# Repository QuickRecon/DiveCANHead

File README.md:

# DiveCAN Head

Open hardware and firmware for a DiveCAN-compatible closed-circuit rebreather
PPO₂ monitor and controller. The firmware supports analog galvanic cells,
DiveO2 and O2S digital cells, solenoid control, runtime configuration,
diagnostics, and persistent telemetry.

## Current development

Active firmware lives in [`Firmware/`](Firmware/) and runs **Zephyr RTOS** on
an STM32L431. It uses MCUboot for updates, Zephyr settings/NVS for persistent
configuration, and flash-backed logs for telemetry and diagnostic text.
The former `STM32/` FreeRTOS application and its build/test directories are no
longer part of this checkout. Earlier implementations and their documentation
remain available in Git history.

Two board targets are defined:

| Board | West target | External storage and power |
|---|---|---|
| DiveCAN Jr | `divecan_jr/stm32l431xx` | 64 MiB SPI NOR; Jr regulator topology |
| DiveCAN MainPCB | `divecan_main/stm32l431xx` | First 64 MiB of a raw SDMMC card; dual-source power mux |

MainPCB's SD adapter supplies the same flash API and partition layout as Jr
for MCUboot, factory backup, settings, and logs. It does not use a filesystem;
the first 64 MiB of the card is firmware-owned and may be overwritten.
See [architecture and board differences](Firmware/ARCHITECTURE.md).

The checked-in software CI builds the five production variants for **Jr**.
MainPCB has a build target, but is not a second board in that CI matrix.
A successful build or simulator test does not establish hardware qualification
or handset compatibility. Numbered releases use a separate HIL qualification
workflow; see [releasing](Firmware/docs/RELEASING.md).

## Is the development environment public?

**The firmware build uses public source and public development tools.** Zephyr,
MCUboot, the STM32 HAL, and the compiler are downloaded separately rather than
copied into this repository. Missing `.west-projects/`, `.west/`, an SDK, or a
Python virtual environment in a fresh clone is expected.

- **West** reads the checked-in `Firmware/west.yml` and downloads the pinned
  Zephyr source and its modules, including MCUboot and the STM32 HAL.
- **Zephyr SDK** provides the ARM compiler/linker used to build STM32 images.
- **Python packages and host tools** run configuration, code generation, and tests.

No private module, paid IDE, GitHub Actions runner, SonarCloud token, or physical
test rig is required to compile the checked-in production variants. The
`Firmware/proprietary/` directory is an optional extension hook, not a missing
part of the standard firmware. Physical HIL/release qualification uses a
private, hardware-dependent Test Rig repository and bench. It is a core pillar
of the safety case, although it is not required for local builds or native
module tests. See [HIL and the safety case](docs/TESTING_ARCHITECTURE.md#hil-is-a-core-pillar-of-the-safety-case).

**New contributor? Follow [Development setup: fresh clone to first build](docs/DEVELOPMENT_SETUP.md).**
It includes host packages, a Python environment, dependency downloads, SDK
installation, a hardware-free test, and troubleshooting. You can compile and
run native tests without owning a board.

## Repository map

| Path | Contents |
|---|---|
| [`Firmware/`](Firmware/) | Zephyr application, board definitions, drivers, variants, tests, and MCUboot configuration |
| [`EDA/`](EDA/) | Electronic design sources and board exports |
| [`CAD/`](CAD/) | Mechanical design assets |
| [`DiveCAN_bt/`](DiveCAN_bt/) | Browser BLE/SLIP/ISO-TP/UDS client, tools, and JavaScript tests |
| [`docs/`](docs/README.md) | Current documentation index and subsystem guides |
| [`.github/workflows/`](.github/workflows/) | Software CI, HIL, release, and KiCad checks |

## Build firmware

After completing the [first-time setup](docs/DEVELOPMENT_SETUP.md), use the revision pinned by [`Firmware/west.yml`](Firmware/west.yml) and the SDK
version in `.west-projects/zephyr/SDK_VERSION`. The current pin is Zephyr 4.4.1
with SDK 1.0.1. Install Python, West, CMake, Ninja, a host C/C++ toolchain, and
the device-tree compiler before configuring the workspace. The exact CI
package and Python dependency setup is in
[the build workflow](.github/workflows/build.yml).

From the repository root, initialise a new West workspace once:

```bash
west init -l Firmware
west update --narrow
west zephyr-export
west packages pip --install
cat .west-projects/zephyr/SDK_VERSION
```

Skip `west init` if the checkout already has `.west/`. Select an installed SDK
matching that version; do not reuse the old NCS toolchain path from historical
notes. To build the Poseidon configuration for Jr:

```bash
cd Firmware
export ZEPHYR_SDK_INSTALL_DIR=/absolute/path/to/zephyr-sdk-1.0.1
export ZEPHYR_TOOLCHAIN_VARIANT=zephyr
west build -d build -b divecan_jr/stm32l431xx . --sysbuild -p always -- \
  -DBOARD_ROOT=. \
  -DEXTRA_CONF_FILE=variants/Poseidon_Aren.conf \
  -DEXTRA_DTC_OVERLAY_FILE=variants/Poseidon_Aren.overlay
```

Always pass the matching `.conf` **and** `.overlay`: the overlay disables unused
peripherals and selects ADC ranges. Use a pristine build when changing board,
variant, or toolchain. For MainPCB, use `-b divecan_main/stm32l431xx` and a
separate directory such as `-d build-main`. A board target selects physical
wiring; a variant selects the fitted cell/control topology. Building a pair
does not prove that its configured outputs exist on the assembled hardware.

The five production variants are `Poseidon_Aren`, `AP_Aren`, `AP_Paul`,
`eCCR_classic`, and `Sidewinder_Gabriel`. `TECME` (3× DiveO2, single O2
solenoid, PID, total absolute cal, 2S) is built by CI but not yet released or
HIL-qualified. `Poseidon_TransducerTest` is a bench
variant with a deliberately scaled pressure-input window, not a production
calibration.

Sysbuild produces:

- `build/merged_divecan_jr_stm32l431xx.hex`: MCUboot plus application for SWD;
- `build/Firmware/zephyr/zephyr.signed.bin`: application image for UDS OTA;
- `build/Firmware/zephyr/zephyr.elf`: application symbols for debugging.

MainPCB uses `merged_divecan_main_stm32l431xx.hex` in its build directory.
See [flashing firmware](docs/FLASHING_FIRMWARE.md) for image selection and the
Jr-specific helper script.

## Test and inspect

Native tests use Zephyr `ztest` on `native_sim`. From `Firmware/`:

```bash
python3 scripts/native_test.py list
ZEPHYR_TOOLCHAIN_VARIANT=host python3 scripts/native_test.py build sd_flash
python3 scripts/native_test.py run sd_flash
# Build and run the full native suite:
ZEPHYR_TOOLCHAIN_VARIANT=host python3 scripts/native_test.py run-all
```

Builds live under `Firmware/build-native/`. The simulator integration harness
and coverage pipeline are separate from the physical HIL bench. See
[testing](docs/TESTING_ARCHITECTURE.md) and
[the HIL workflow](docs/HIL_GITHUB_ACTIONS.md).

Browser client tests run from `DiveCAN_bt/`:

```bash
npm ci
npm run test:run
```

## Documentation

Start with the [documentation index](docs/README.md). Frequently used guides:

- [Firmware architecture](Firmware/ARCHITECTURE.md): board topology, storage,
  threads, power, sensors, control, and build design.
- [UDS wire reference](Firmware/UDS.md) and [DID catalogue](docs/DATA_IDENTIFIERS.md).
- [Flash logs](Firmware/docs/FLASH_LOG.md) and
  [telemetry viewer/CLI](docs/TELEMETRY_VIEWER.md).
- [Browser client](DiveCAN_bt/README.md).
- [Release process and download contents](Firmware/docs/RELEASING.md).
- [Engineering compromises](Firmware/COMPROMISE.md) and
  [bench-test checklist](Firmware/BENCHTEST.md).

DiveCAN is Shearwater's proprietary rebreather communications bus. This project
implements compatible messaging; protocol research is maintained in the
[QuickRecon DiveCAN repository](https://github.com/QuickRecon/DiveCAN).
Compatibility must be established for the particular handset and configuration.

Contributions and issue reports are welcome. Include the board, variant,
firmware revision, and relevant diagnostics when reporting behavior.

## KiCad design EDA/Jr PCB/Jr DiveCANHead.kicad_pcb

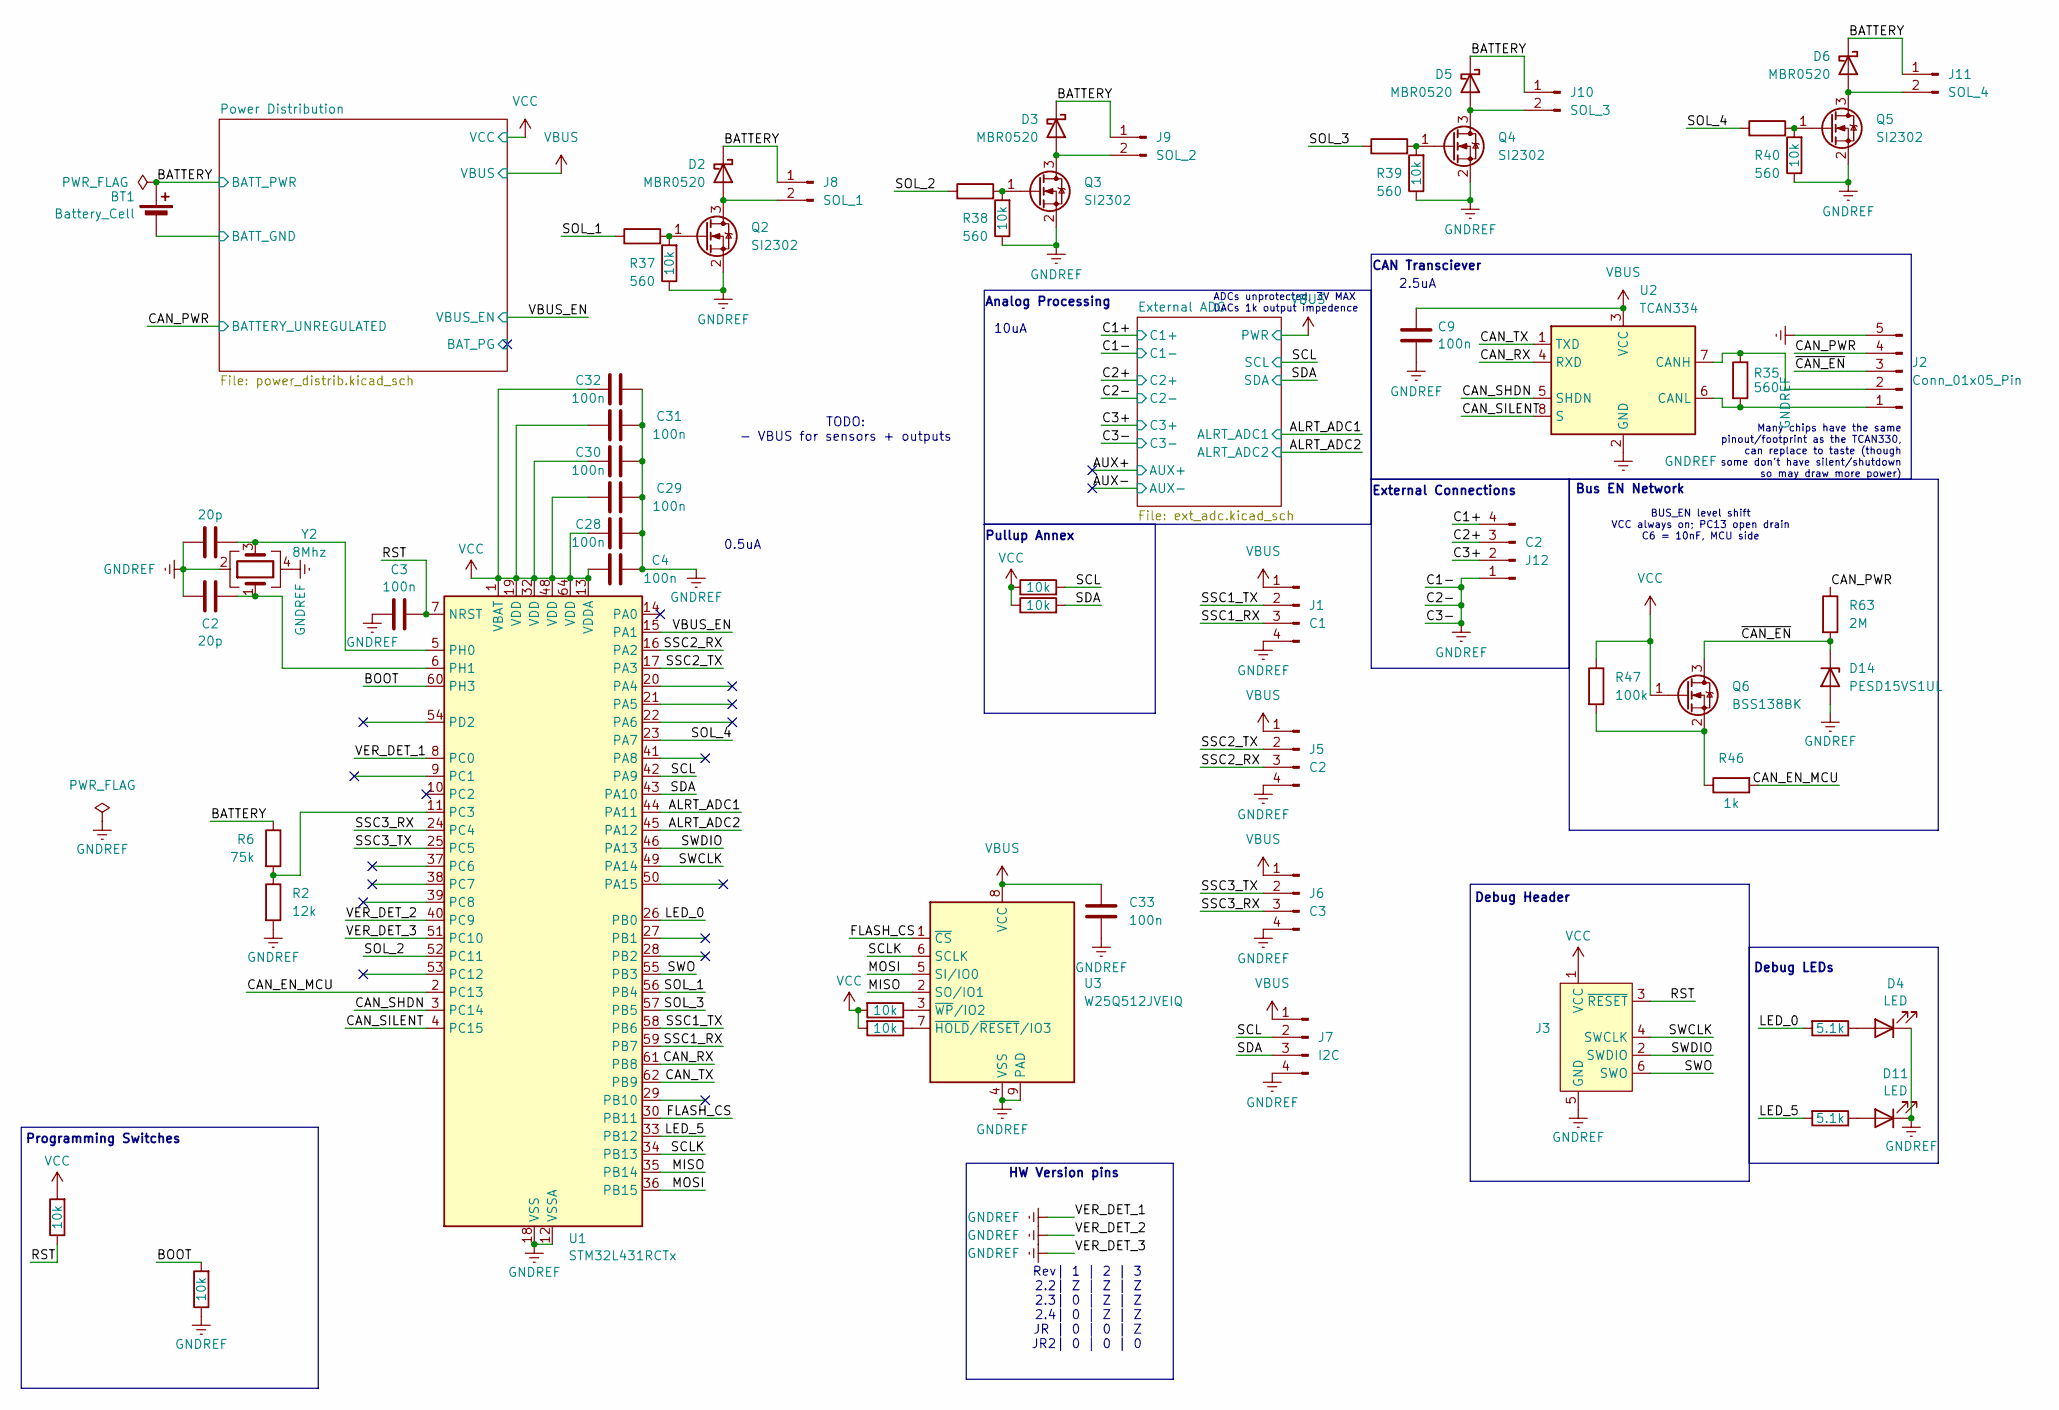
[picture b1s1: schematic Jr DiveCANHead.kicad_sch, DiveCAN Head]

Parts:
BT1: Battery_Cell; BatteryHolder_Eagle_12BH611-GR
C1, C2: 20p; C_0603_1608Metric; MPN C325469
C3, C4, C9, C28, C29, C30, C31, C32, C33: 100n; C_0603_1608Metric; MPN C14663
D2, D3, D5, D6: MBR0520; D_SOD-123; MPN C5204745
D4, D11: LED; LED_0805_2012Metric; MPN C84256
D14: PESD15VS1UL; D_SOD-882; MPN C552453
J1: C1; PinHeader_1x04_P2.54mm_Vertical
J2: Conn_01x05_Pin; PinHeader_1x05_P2.54mm_Hole1.25mm_Pad1.95mm
J3: Conn_ARM_SWD_TagConnect_TC2030-NL; Tag-Connect_TC2030-IDC-NL_2x03_P1.27mm_Vertical
J5, J12: C2; PinHeader_1x04_P2.54mm_Vertical
J6: C3; PinHeader_1x04_P2.54mm_Vertical
J7: I2C; PinHeader_1x04_P2.54mm_Vertical
J8: SOL_1; PinHeader_1x02_P2.54mm_Vertical
J9: SOL_2; PinHeader_1x02_P2.54mm_Vertical
J10: SOL_3; PinHeader_1x02_P2.54mm_Vertical
J11: SOL_4; PinHeader_1x02_P2.54mm_Vertical
Q2, Q3, Q4, Q5: SI2302; SOT-23; MPN C181087; JlcRotOffset 180
Q6: BSS138BK; SOT-23; MPN C282529; JlcRotOffset 180
R1, R3, R4, R5, R7, R8, R9, R10, R11, R12: 10k; R_0402_1005Metric; MPN C25744
R2: 12k; R_0402_1005Metric; MPN C25752
R6: 75k; R_0402_1005Metric; MPN C25798
R35: 560; R_0603_1608Metric; MPN C23204
R36, R43: 5.1k; R_0402_1005Metric; MPN C25905
R37, R38, R39, R40: 560; R_0402_1005Metric; MPN C163460
R46: 1k; R_0402_1005Metric; MPN C11702
R47: 100k; R_0402_1005Metric; MPN C25741
R63: 2M; R_0603_1608Metric; MPN C22976
U1: STM32L431RCTx; LQFP-64_10x10mm_P0.5mm; JLC C92468
U2: TCAN334; SOIC-8_3.9x4.9mm_P1.27mm; MPN C2871143; JlcRotOffset -90
U3: W25Q512JVEIQ; WSON-8-1EP_8x6mm_P1.27mm_EP3.4x4.3mm; MPN C7389628
Y2: 8Mhz; Crystal_SMD_3225-4Pin_3.2x2.5mm; MPN C648987

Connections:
/ALRT_ADC1: U1.44 (PA11); also elsewhere on the board
/ALRT_ADC2: U1.45 (PA12); also elsewhere on the board
/BATTERY: BT1.1 (+), D2.1 (K), D3.1 (K), D5.1 (K), D6.1 (K), J8.1, J9.1, J10.1, J11.1, R6.1; also elsewhere on the board
/BOOT: R4.2, U1.60 (PH3)
/C1+: J12.4; also elsewhere on the board
/C2+: J12.3; also elsewhere on the board
/C3+: J12.2; also elsewhere on the board
/CAN_EN_MCU: R46.2, U1.2 (PC13)
/CAN_PWR: J2.4, R63.1; also elsewhere on the board
/CAN_RX: U1.61 (PB8), U2.4 (RXD)
/CAN_SHDN: U1.3 (PC14), U2.5 (SHDN)
/CAN_SILENT: U1.4 (PC15), U2.8 (S)
/CAN_TX: U1.62 (PB9), U2.1 (TXD)
/FLASH_CS: U1.30 (PB11), U3.1 (~CS)
/LED_0: R36.2, U1.26 (PB0)
/LED_5: R43.2, U1.33 (PB12)
/MISO: U1.35 (PB14), U3.2 (SO/IO1)
/MOSI: U1.36 (PB15), U3.5 (SI/IO0)
/Power Distribution/BATT_GND: BT1.2 (-); also elsewhere on the board
/RST: C3.2, J3.3 (~RESET), R1.1, U1.7 (NRST)
/SCL: J7.2, R7.2, U1.42 (PA9); also elsewhere on the board
/SCLK: U1.34 (PB13), U3.6 (SCLK)
/SDA: J7.3, R8.2, U1.43 (PA10); also elsewhere on the board
/SOL_1: R37.1, U1.56 (PB4)
/SOL_2: R38.1, U1.52 (PC11)
/SOL_3: R39.1, U1.57 (PB5)
/SOL_4: R40.1, U1.23 (PA7)
/SSC1_RX: J1.3, U1.59 (PB7)
/SSC1_TX: J1.2, U1.58 (PB6)
/SSC2_RX: J5.3, U1.16 (PA2)
/SSC2_TX: J5.2, U1.17 (PA3)
/SSC3_RX: J6.3, U1.24 (PC4)
/SSC3_TX: J6.2, U1.25 (PC5)
/SWCLK: J3.4 (SWCLK), U1.49 (PA14)
/SWDIO: J3.2 (SWDIO), U1.46 (PA13)
/SWO: J3.6 (SWO), U1.55 (PB3)
/VBUS_EN: U1.15 (PA1); also elsewhere on the board
/~CAN_EN: D14.1 (K), J2.3, Q6.3 (D), R63.2
GNDREF: C1.1, C2.1, C3.1, C4.1, C9.2, C28.1, C29.1, C30.1, C31.1, C32.1, C33.2, D4.1 (K), D11.1 (K), D14.2 (A), J1.4, J2.5, J3.5 (GND), J5.4, J6.4, J7.4, J12.1, Q2.2 (S), Q3.2 (S), Q4.2 (S), Q5.2 (S), R2.2, R3.1, R4.1, R5.1, R9.1, R10.1, U1.8 (PC0), U1.12 (VSSA), U1.18 (VSS), U1.31 (VSS), U1.40 (PC9), U1.47 (VSS), U1.51 (PC10), U1.63 (VSS), U2.2 (GND), U3.4 (VSS), U3.9 (PAD), Y2.2, Y2.4; also elsewhere on the board
unnamed: D2.2 (A), J8.2, Q2.3 (D)
unnamed: D3.2 (A), J9.2, Q3.3 (D)
unnamed: D4.2 (A), R36.1
unnamed: D5.2 (A), J10.2, Q4.3 (D)
unnamed: D6.2 (A), J11.2, Q5.3 (D)
unnamed: D11.2 (A), R43.1
unnamed: J2.1, R35.2, U2.6 (CANL)
unnamed: J2.2, R35.1, U2.7 (CANH)
unnamed: Q2.1 (G), R3.2, R37.2
unnamed: Q3.1 (G), R5.2, R38.2
unnamed: Q4.1 (G), R9.2, R39.2
unnamed: Q5.1 (G), R10.2, R40.2
unnamed: Q6.2 (S), R46.1, R47.2
unnamed: R2.1, R6.2, U1.11 (PC3)
unnamed: C1.2, U1.5 (PH0), Y2.3
unnamed: C2.2, U1.6 (PH1), Y2.1
unnamed: R12.1, U3.7 (~HOLD/~RESET/IO3)
unnamed: R11.1, U3.3 (~WP/IO2)
VBUS: C9.1, C33.1, J1.1, J5.1, J6.1, J7.1, U2.3 (VCC), U3.8 (VCC); also elsewhere on the board
VCC: C4.2, C28.2, C29.2, C30.2, C31.2, C32.2, J3.1 (VCC), Q6.1 (G), R1.2, R7.1, R8.1, R11.2, R12.2, R47.1, U1.1 (VBAT), U1.13 (VDDA), U1.19 (VDD), U1.32 (VDD), U1.48 (VDD), U1.64 (VDD); also elsewhere on the board

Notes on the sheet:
10uA
Many chips have the same pinout/footprint as the TCAN330, can replace to taste (though some don't have silent/shutdown so may draw more power)
HW Version pins
Pullup Annex
External Connections
TODO: - VBUS for sensors + outputs
ADCs unprotected, 3V MAX DACs 1k output impedence
Programming Switches
BUS_EN level shift VCC always on; PC13 open drain C6 = 10nF, MCU side
Debug LEDs
0.5uA
Rev| 1 | 2 | 3 2.2| Z | Z | Z 2.3| 0 | Z | Z 2.4| 0 | Z | Z JR | 0 | 0 | Z JR2| 0 | 0 | 0
CAN Transciever
Debug Header
Analog Processing
2.5uA
Bus EN Network

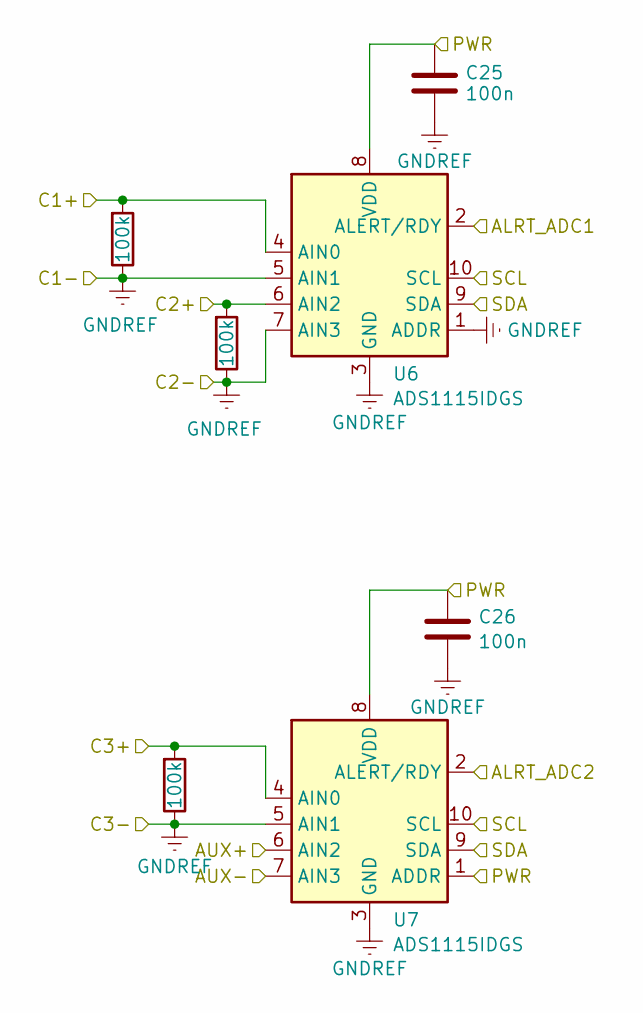
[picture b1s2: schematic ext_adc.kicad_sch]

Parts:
C25, C26: 100n; C_0603_1608Metric; MPN C14663
R13, R14, R15: 100k; R_0402_1005Metric; MPN C25741
U6, U7: ADS1115IDGS; TSSOP-10_3x3mm_P0.5mm; JLC C468683

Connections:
/ALRT_ADC1: U6.2 (ALERT/RDY); also elsewhere on the board
/ALRT_ADC2: U7.2 (ALERT/RDY); also elsewhere on the board
/AUX+: U7.6 (AIN2)
/AUX-: U7.7 (AIN3)
/C1+: R15.2, U6.4 (AIN0); also elsewhere on the board
/C2+: R14.2, U6.6 (AIN2); also elsewhere on the board
/C3+: R13.2, U7.4 (AIN0); also elsewhere on the board
/SCL: U6.10 (SCL), U7.10 (SCL); also elsewhere on the board
/SDA: U6.9 (SDA), U7.9 (SDA); also elsewhere on the board
GNDREF: C25.2, C26.2, R13.1, R14.1, R15.1, U6.1 (ADDR), U6.3 (GND), U6.5 (AIN1), U6.7 (AIN3), U7.3 (GND), U7.5 (AIN1); also elsewhere on the board
VBUS: C25.1, C26.1, U6.8 (VDD), U7.1 (ADDR), U7.8 (VDD); also elsewhere on the board

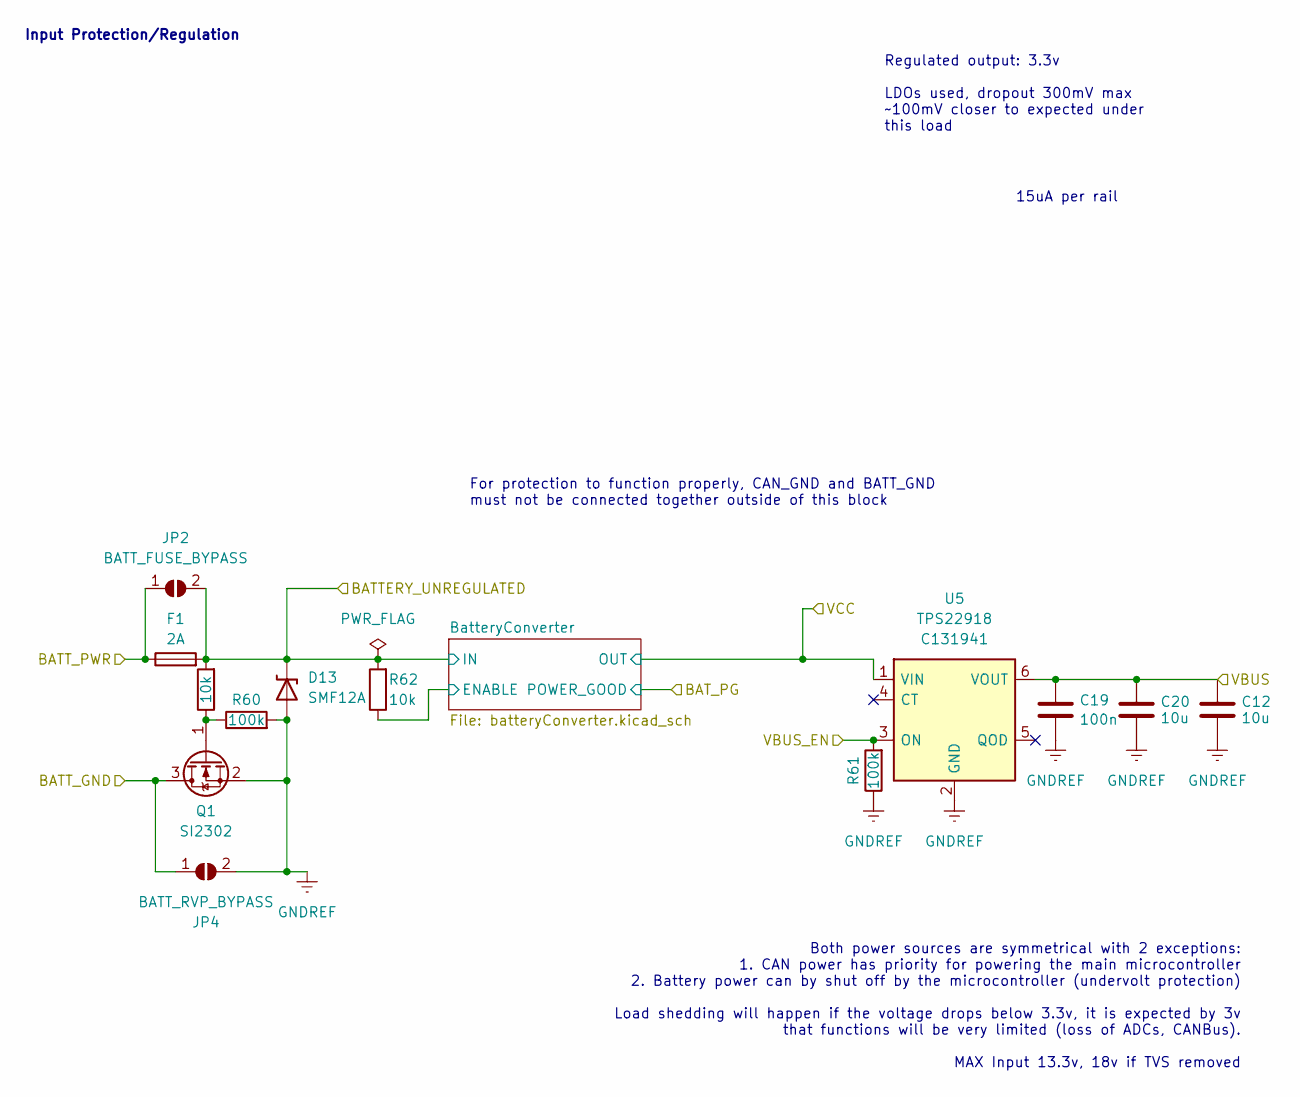
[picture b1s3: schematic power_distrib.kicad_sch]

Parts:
C12, C20: 10u; C_0603_1608Metric; MPN C96446
C19: 100n; C_0603_1608Metric; MPN C14663
D13: SMF12A; D_SOD-123F; MPN C178259
F1: 2A; Fuseholder_Littelfuse_Nano2_154x; MPN C108518
JP2: BATT_FUSE_BYPASS; SolderJumper-2_P1.3mm_Open_TrianglePad1.0x1.5mm
JP4: BATT_RVP_BYPASS; SolderJumper-2_P1.3mm_Open_TrianglePad1.0x1.5mm
Q1: SI2302; SOT-23; MPN C181087; JlcRotOffset 180
R58, R62: 10k; R_0402_1005Metric; MPN C25744
R60, R61: 100k; R_0402_1005Metric; MPN C25741
U5: TPS22918; SOT-23-6; JLC Part # C131941

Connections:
/BATTERY: F1.1, JP2.1 (A); also elsewhere on the board
/CAN_PWR: D13.1 (A1), F1.2, JP2.2 (B), R58.2, R62.2; also elsewhere on the board
/Power Distribution/BATT_GND: JP4.1 (A), Q1.3 (D); also elsewhere on the board
/Power Distribution/BatteryConverter/ENABLE: R62.1; also elsewhere on the board
/VBUS_EN: R61.2, U5.3 (ON); also elsewhere on the board
GNDREF: C12.2, C19.2, C20.2, D13.2 (A2), JP4.2 (B), Q1.2 (S), R60.2, R61.1, U5.2 (GND); also elsewhere on the board
unnamed: Q1.1 (G), R58.1, R60.1
VBUS: C12.1, C19.1, C20.1, U5.6 (VOUT); also elsewhere on the board
VCC: U5.1 (VIN); also elsewhere on the board

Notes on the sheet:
Both power sources are symmetrical with 2 exceptions: 1. CAN power has priority for powering the main microcontroller 2. Battery power can by shut off by the microcontroller (undervolt protection) Load shedding will happen if the voltage drops below 3.3v, it is expected by 3v that functions will be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
15uA per rail
Input Protection/Regulation
Regulated output: 3.3v LDOs used, dropout 300mV max ~100mV closer to expected under this load
For protection to function properly, CAN_GND and BATT_GND must not be connected together outside of this block

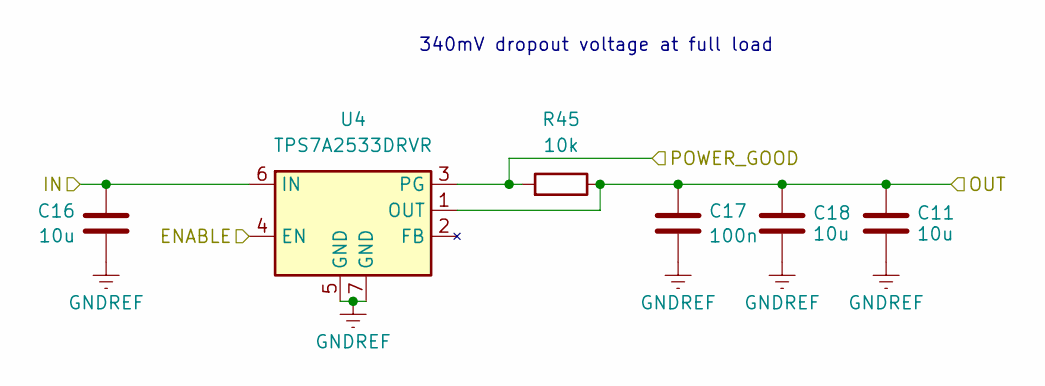
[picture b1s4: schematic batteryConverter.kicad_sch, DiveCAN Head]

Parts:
C11, C16, C18: 10u; C_0603_1608Metric; MPN C96446
C17: 100n; C_0603_1608Metric; MPN C14663
R45: 10k; R_0402_1005Metric; MPN C25744
U4: TPS7A2533DRVR; WSON-6_2x2mm_P0.65mm_EP_NoThermalVias_Jr; MPN C2867820; JlcRotOffset 0

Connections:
/CAN_PWR: C16.1, U4.6 (IN); also elsewhere on the board
/Power Distribution/BAT_PG: R45.2, U4.3 (PG)
/Power Distribution/BatteryConverter/ENABLE: U4.4 (EN); also elsewhere on the board
GNDREF: C11.2, C16.2, C17.2, C18.2, U4.5 (GND), U4.7 (GND); also elsewhere on the board
VCC: C11.1, C17.1, C18.1, R45.1, U4.1 (OUT); also elsewhere on the board

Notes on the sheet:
340mV dropout voltage at full load

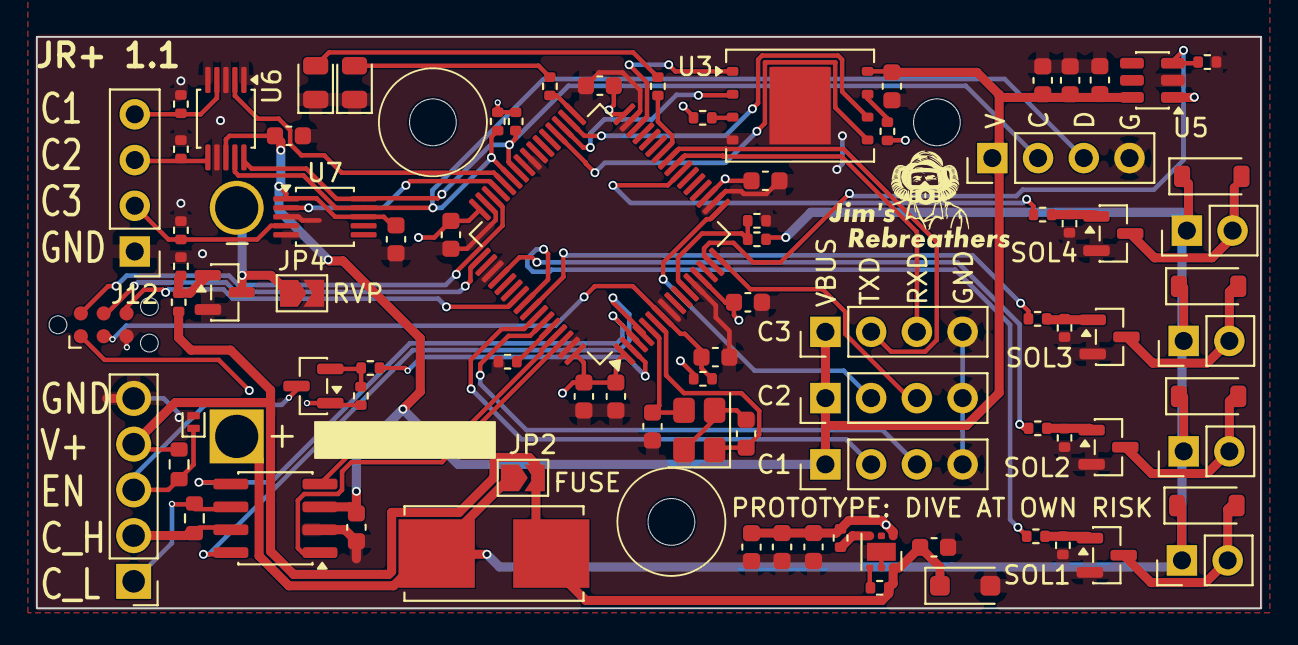
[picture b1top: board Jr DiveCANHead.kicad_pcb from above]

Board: 2 copper layers, 68.0 x 31.7 mm, 87 parts (1 on the bottom side), 62 nets.

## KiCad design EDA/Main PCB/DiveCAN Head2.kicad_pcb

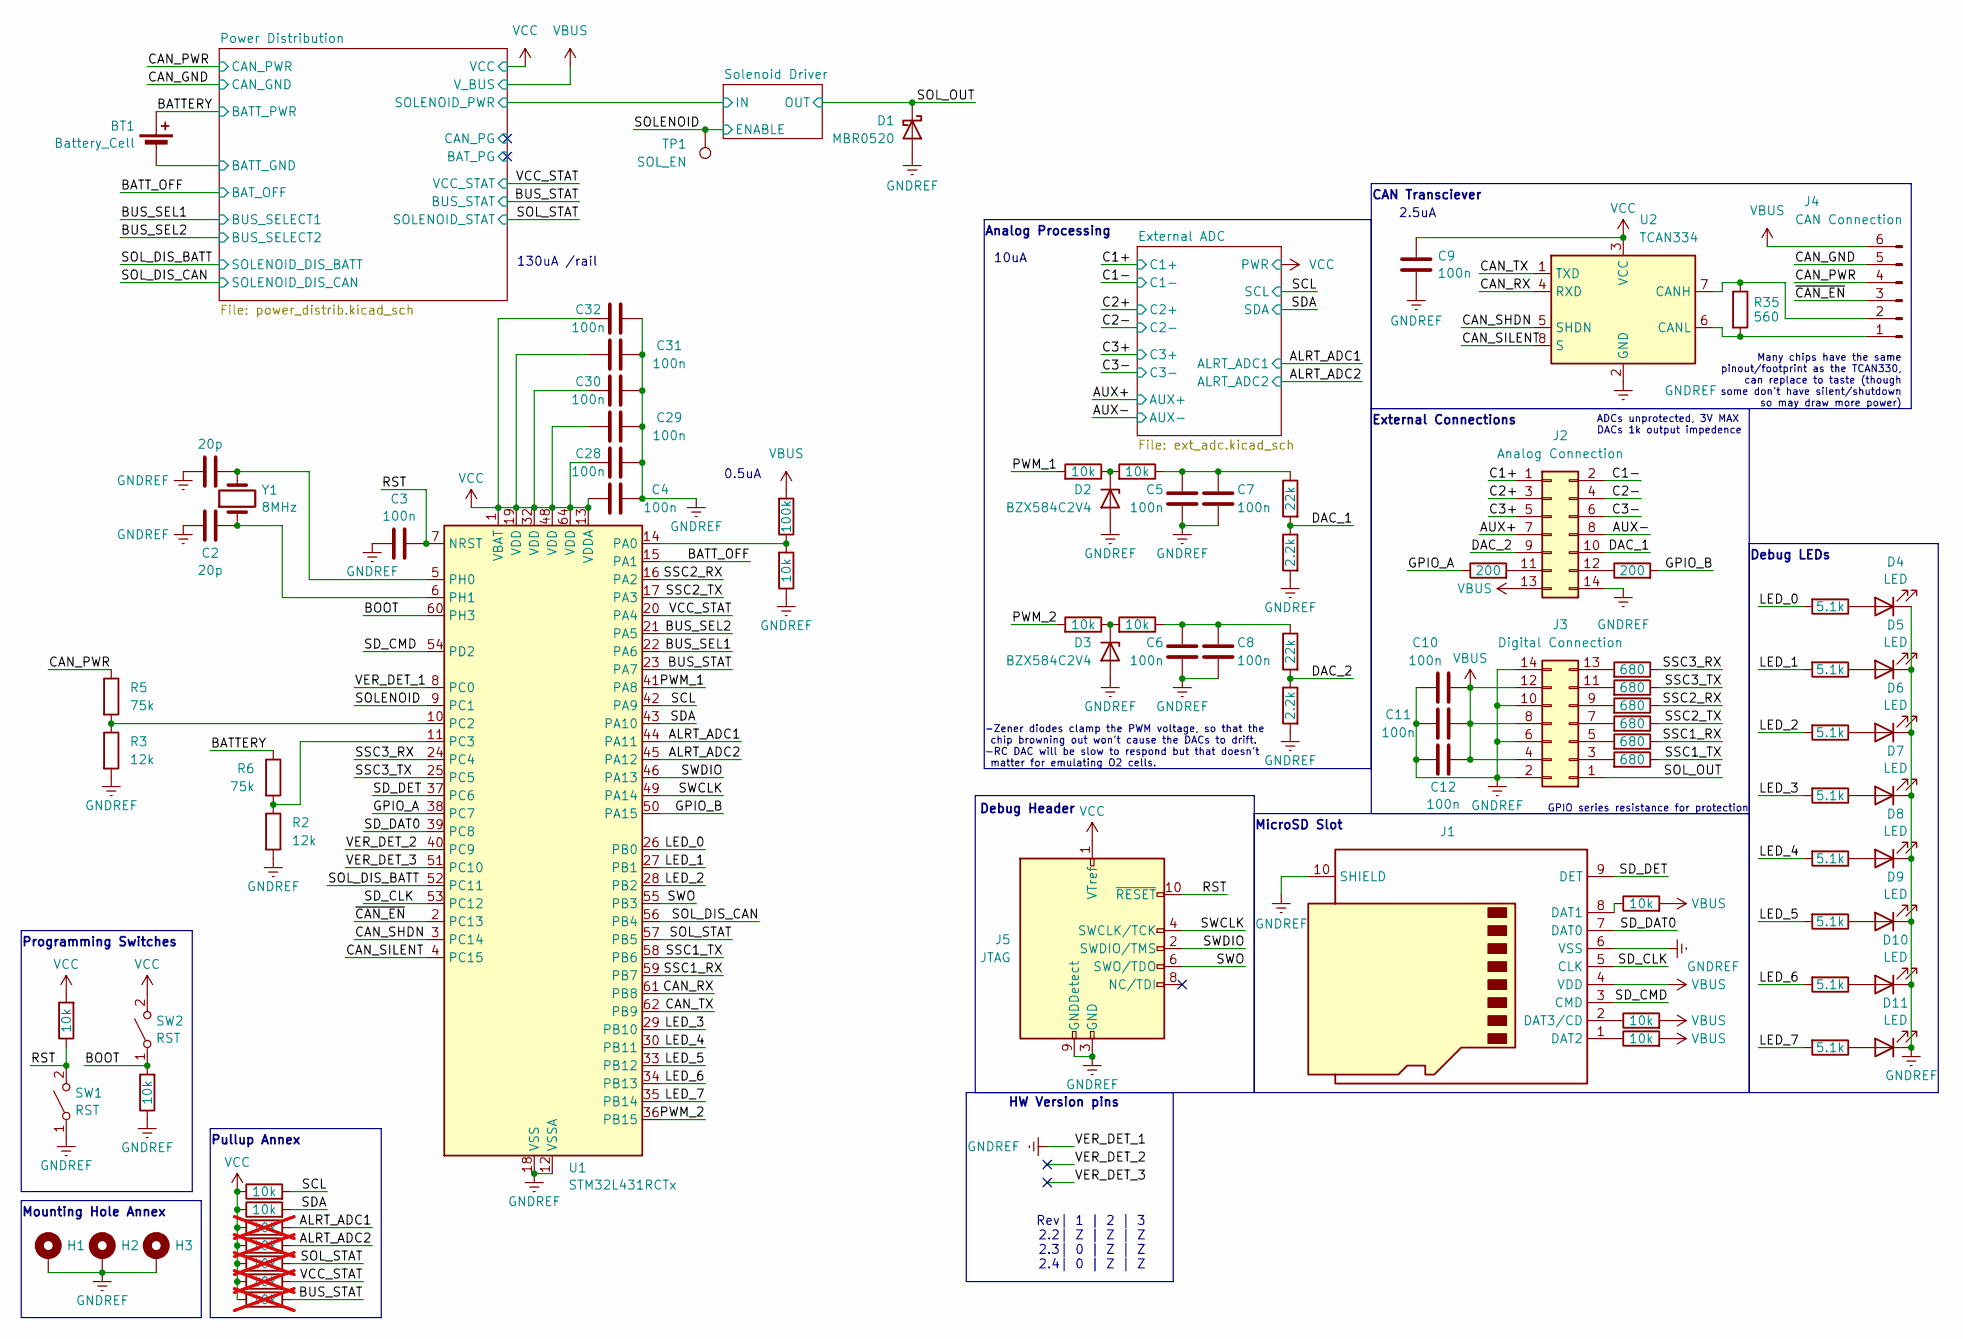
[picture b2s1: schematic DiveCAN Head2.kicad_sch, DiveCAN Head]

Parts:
BT1: Battery_Cell; PinHeader_1x02_P2.54mm_Horizontal
C1, C2: 20p; C_0603_1608Metric; MPN C325469
C3, C4, C5, C6, C7, C8, C9, C10, C11, C12, C28, C29, C30, C31, C32: 100n; C_0603_1608Metric; MPN C14663
D1: MBR0520; D_SOD-123; MPN C5204745
D2, D3: BZX584C2V4; D_SOD-523; MPN C968191
D4, D5, D6, D7, D8, D9, D10, D11: LED; LED_0805_2012Metric; MPN C84256
H1, H2, H3: MountingHole_Pad; MountingHole_3.2mm_M3_Pad
J1: Micro_SD_Card_Det1; CONN9_0185-02_GSW; MPN C5155564
J2: Analog Connection; IDC-Header_2x07_P2.54mm_Vertical
J3: Digital Connection; IDC-Header_2x07_P2.54mm_Vertical
J4: CAN Connection; PinHeader_1x06_P2.54mm_Horizontal
J5: JTAG; CON10_2X5_DUK_FTSH_SAI; MPN C448647
R1, R4, R7, R8, R15, R16, R17, R18, R19, R32, R33, R34: 10k; R_0402_1005Metric; MPN C25744
R2, R3: 12k; R_0402_1005Metric; MPN C25752
R5, R6: 75k; R_0402_1005Metric; MPN C25798
R9, R10, R11, R12, R13: 10k; R_0402_1005Metric; MPN C25744; not fitted
R14: 100k; R_0402_1005Metric; MPN C25741
R20, R22: 22k; R_0402_1005Metric; MPN C25768
R21, R23: 2.2k; R_0402_1005Metric; MPN C25879
R24, R25: 200; R_0402_1005Metric; MPN C25087
R26, R27, R28, R29, R30, R31: 680; R_0402_1005Metric; MPN C25130
R35: 560; R_0603_1608Metric; MPN C23204
R36, R37, R38, R39, R40, R41, R42, R43: 5.1k; R_0402_1005Metric; MPN C25905
SW1, SW2: RST; SW_SPST_EVQPE1; MPN C2915176
TP1: SOL_EN; TestPoint_THTPad_D1.0mm_Drill0.5mm
U1: STM32L431RCTx; LQFP-64_10x10mm_P0.5mm; JLC C92468
U2: TCAN334; SOIC-8_3.9x4.9mm_P1.27mm; MPN C2871143; JlcRotOffset -90
Y1: 8MHz; Crystal_SMD_HC49-SD; MPN C963524

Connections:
/ALRT_ADC1: R9.2, U1.44 (PA11); also elsewhere on the board
/ALRT_ADC2: R10.2, U1.45 (PA12); also elsewhere on the board
/AUX+: J2.7; also elsewhere on the board
/AUX-: J2.8; also elsewhere on the board
/BATTERY: BT1.1 (+), R6.1; also elsewhere on the board
/BATT_OFF: U1.15 (PA1); also elsewhere on the board
/BOOT: R4.2, SW2.1 (A), U1.60 (PH3)
/BUS_SEL1: U1.22 (PA6); also elsewhere on the board
/BUS_SEL2: U1.21 (PA5); also elsewhere on the board
/BUS_STAT: R13.2, U1.23 (PA7); also elsewhere on the board
/C1+: J2.1; also elsewhere on the board
/C1-: J2.2; also elsewhere on the board
/C2+: J2.3; also elsewhere on the board
/C2-: J2.4; also elsewhere on the board
/C3+: J2.5; also elsewhere on the board
/C3-: J2.6; also elsewhere on the board
/CAN_GND: J4.5; also elsewhere on the board
/CAN_PWR: J4.4, R5.1; also elsewhere on the board
/CAN_RX: U1.61 (PB8), U2.4 (RXD)
/CAN_SHDN: U1.3 (PC14), U2.5 (SHDN)
/CAN_SILENT: U1.4 (PC15), U2.8 (S)
/CAN_TX: U1.62 (PB9), U2.1 (TXD)
/DAC_1: J2.10, R20.2, R21.1
/DAC_2: J2.9, R22.2, R23.1
/GPIO_A: R24.1, U1.38 (PC7)
/GPIO_B: R25.2, U1.50 (PA15)
/LED_0: R36.2, U1.26 (PB0)
/LED_1: R37.2, U1.27 (PB1)
/LED_2: R38.2, U1.28 (PB2)
/LED_3: R39.2, U1.29 (PB10)
/LED_4: R40.2, U1.30 (PB11)
/LED_5: R41.2, U1.33 (PB12)
/LED_6: R42.2, U1.34 (PB13)
/LED_7: R43.2, U1.35 (PB14)
/PWM_1: R16.2, U1.41 (PA8)
/PWM_2: R17.2, U1.36 (PB15)
/Power Distribution/BATT_GND: BT1.2 (-); also elsewhere on the board
/RST: C3.2, J5.10 (~RESET), R1.1, SW1.2 (B), U1.7 (NRST)
/SCL: R7.2, U1.42 (PA9); also elsewhere on the board
/SDA: R8.2, U1.43 (PA10); also elsewhere on the board
/SD_CLK: J1.5 (CLK), U1.53 (PC12)
/SD_CMD: J1.3 (CMD), U1.54 (PD2)
/SD_DAT0: J1.7 (DAT0), U1.39 (PC8)
/SD_DET: J1.9 (DET), U1.37 (PC6)
/SOLENOID: TP1.1, U1.9 (PC1); also elsewhere on the board
/SOL_DIS_BATT: U1.52 (PC11); also elsewhere on the board
/SOL_DIS_CAN: U1.56 (PB4); also elsewhere on the board
/SOL_OUT: D1.1 (K), J3.1; also elsewhere on the board
/SOL_STAT: R11.2, U1.57 (PB5); also elsewhere on the board
/SSC1_RX: R30.1, U1.59 (PB7)
/SSC1_TX: R31.1, U1.58 (PB6)
/SSC2_RX: R28.1, U1.16 (PA2)
/SSC2_TX: R29.1, U1.17 (PA3)
/SSC3_RX: R26.1, U1.24 (PC4)
/SSC3_TX: R27.1, U1.25 (PC5)
/SWCLK: J5.4 (SWCLK/TCK), U1.49 (PA14)
/SWDIO: J5.2 (SWDIO/TMS), U1.46 (PA13)
/SWO: J5.6 (SWO/TDO), U1.55 (PB3)
/VCC_STAT: R12.2, U1.20 (PA4); also elsewhere on the board
/VER_DET_2: U1.40 (PC9)
/VER_DET_3: U1.51 (PC10)
/~CAN_EN: J4.3, U1.2 (PC13)
GNDREF: C1.1, C2.1, C3.1, C4.1, C5.1, C6.1, C7.1, C8.1, C9.2, C10.1, C11.1, C12.1, C28.1, C29.1, C30.1, C31.1, C32.1, D1.2 (A), D2.2 (A), D3.2 (A), D4.1 (K), D5.1 (K), D6.1 (K), D7.1 (K), D8.1 (K), D9.1 (K), D10.1 (K), D11.1 (K), H1.1, H2.1, H3.1, J1.6 (VSS), J1.10 (SHIELD), J2.14, J3.2, J3.6, J3.10, J3.14, J5.3 (GND), J5.5 (GND), J5.9 (GNDDetect), R2.2, R3.2, R4.1, R15.1, R21.2, R23.2, SW1.1 (A), U1.8 (PC0), U1.12 (VSSA), U1.18 (VSS), U1.31 (VSS), U1.47 (VSS), U1.63 (VSS), U2.2 (GND); also elsewhere on the board
unnamed: C5.2, C7.2, R18.1, R20.1
unnamed: C6.2, C8.2, R19.1, R22.1
unnamed: D2.1 (K), R16.1, R18.2
unnamed: D3.1 (K), R17.1, R19.2
unnamed: D4.2 (A), R36.1
unnamed: D5.2 (A), R37.1
unnamed: D6.2 (A), R38.1
unnamed: D7.2 (A), R39.1
unnamed: D8.2 (A), R40.1
unnamed: D9.2 (A), R41.1
unnamed: D10.2 (A), R42.1
unnamed: D11.2 (A), R43.1
unnamed: J1.8 (DAT1), R32.1
unnamed: J1.1 (DAT2), R34.1
unnamed: J1.2 (DAT3/CD), R33.1
unnamed: J2.11, R24.2
unnamed: J2.12, R25.1
unnamed: J3.3, R31.2
unnamed: J3.5, R30.2
unnamed: J3.7, R29.2
unnamed: J3.9, R28.2
unnamed: J3.11, R27.2
unnamed: J3.13, R26.2
unnamed: J4.1, R35.2, U2.6 (CANL)
unnamed: J4.2, R35.1, U2.7 (CANH)
unnamed: R14.1, R15.2, U1.14 (PA0)
unnamed: R3.1, R5.2, U1.10 (PC2)
unnamed: R2.1, R6.2, U1.11 (PC3)
unnamed: C1.2, U1.5 (PH0), Y1.2
unnamed: C2.2, U1.6 (PH1), Y1.1
VBUS: C10.2, C11.2, C12.2, J1.4 (VDD), J2.13, J3.4, J3.8, J3.12, J4.6, R14.2, R32.2, R33.2, R34.2; also elsewhere on the board
VCC: C4.2, C9.1, C28.2, C29.2, C30.2, C31.2, C32.2, J5.1 (VTref), R1.2, R7.1, R8.1, R9.1, R10.1, R11.1, R12.1, R13.1, SW2.2 (B), U1.1 (VBAT), U1.13 (VDDA), U1.19 (VDD), U1.32 (VDD), U1.48 (VDD), U1.64 (VDD), U2.3 (VCC); also elsewhere on the board

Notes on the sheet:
10uA
Many chips have the same pinout/footprint as the TCAN330, can replace to taste (though some don't have silent/shutdown so may draw more power)
HW Version pins
MicroSD Slot
Mounting Hole Annex
Pullup Annex
External Connections
ADCs unprotected, 3V MAX DACs 1k output impedence
Programming Switches
Debug LEDs
0.5uA
GPIO series resistance for protection
Rev| 1 | 2 | 3 2.2| Z | Z | Z 2.3| 0 | Z | Z 2.4| 0 | Z | Z
-Zener diodes clamp the PWM voltage, so that the chip browning out won't cause the DACs to drift. -RC DAC will be slow to respond but that doesn't matter for emulating O2 cells.
CAN Transciever
Debug Header
Analog Processing
2.5uA
130uA /rail

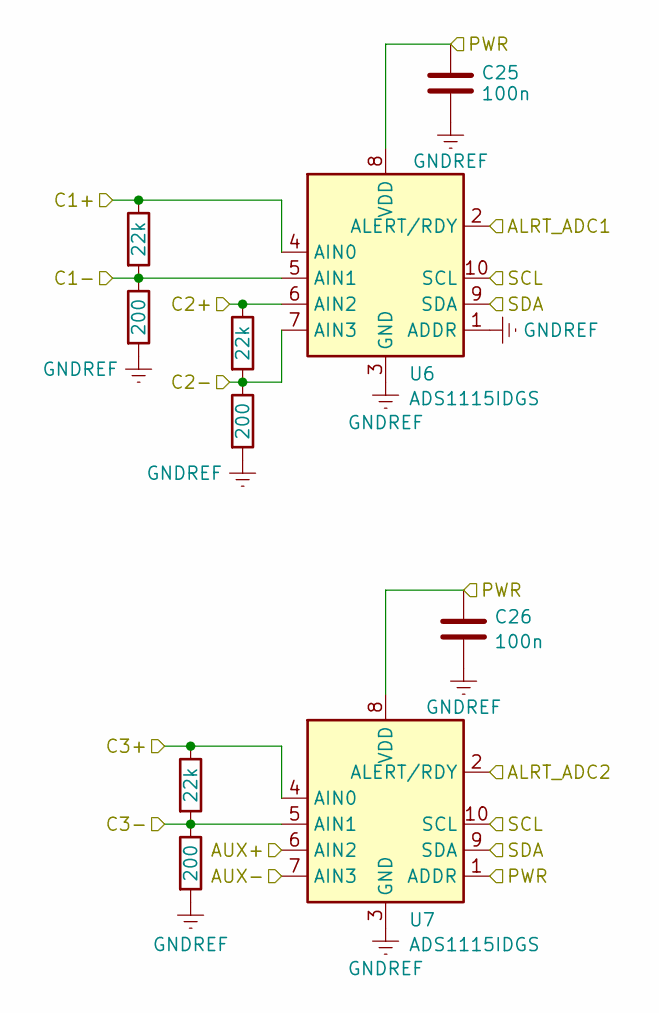
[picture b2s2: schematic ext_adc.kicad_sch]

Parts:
C25, C26: 100n; C_0603_1608Metric; MPN C14663
R52, R54, R56: 22k; R_0402_1005Metric; MPN C25768
R53, R55, R57: 200; R_0402_1005Metric; MPN C25087
U6, U7: ADS1115IDGS; TSSOP-10_3x3mm_P0.5mm; JLC C37593

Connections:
/ALRT_ADC1: U6.2 (ALERT/RDY); also elsewhere on the board
/ALRT_ADC2: U7.2 (ALERT/RDY); also elsewhere on the board
/AUX+: U7.6 (AIN2); also elsewhere on the board
/AUX-: U7.7 (AIN3); also elsewhere on the board
/C1+: R52.1, U6.4 (AIN0); also elsewhere on the board
/C1-: R52.2, R53.1, U6.5 (AIN1); also elsewhere on the board
/C2+: R56.1, U6.6 (AIN2); also elsewhere on the board
/C2-: R56.2, R57.1, U6.7 (AIN3); also elsewhere on the board
/C3+: R54.1, U7.4 (AIN0); also elsewhere on the board
/C3-: R54.2, R55.1, U7.5 (AIN1); also elsewhere on the board
/SCL: U6.10 (SCL), U7.10 (SCL); also elsewhere on the board
/SDA: U6.9 (SDA), U7.9 (SDA); also elsewhere on the board
GNDREF: C25.2, C26.2, R53.2, R55.2, R57.2, U6.1 (ADDR), U6.3 (GND), U7.3 (GND); also elsewhere on the board
VCC: C25.1, C26.1, U6.8 (VDD), U7.1 (ADDR), U7.8 (VDD); also elsewhere on the board
